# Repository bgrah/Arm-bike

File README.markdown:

Arm bike (ARM7 based system with GPS and graphical UI)
=============================================

Description
-----------

In this project is all about ARM, GPS, LCD, LED and bike. Throw all this together and make right connections and you have got a fine working and usable microcontroler system.
It's meant to be flexsible, modular, easy to use and of course open to all.

More about project description in Entry file below.

Documents
---------

+ [Entry file](https://github.com/blaaz15/Arm-bike/blob/master/project_description.markdown)

Current state:
--------------
+ 23. 4. 2012 -> First prototype PCB for MCU module (still waiting for parts from Farnell (13.5.))
+  1. 5. 2012 -> Started working on software.
+ 11. 5. 2012 -> Realized that the hardware part of project won't be finnished in time (still waiting for parts) :/
+ 13. 5. 2012 -> Software is comming nicely together. Still a lot of work, but its nice to see working things.

Author
------

Blaž Grah

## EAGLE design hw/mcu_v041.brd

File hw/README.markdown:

Arm-bike/hw
===========

TO-DO:
------
+ MCU PCB:
  - Put all pins on headers.
  - Improve design with separate analog and xtal ground.
  - Include mounting holes and round PCB edges.
  - Add schottky diodes on power input
  - Optimize header layout for multi-module layer use
+ SENSOR PCB:
  - Make place for GPS antenna
  - Leave free space for possible later additions (gyro,...)
+ TOUCHPAD PCB
  - Check MPR121 datasheet for touchpad dimensions/layout
  - Make space for LCD module
+ BIKE PCB
  - Design PWM enabled current supply for power LEDs
  - Battery powered with magnetic switch enable?
  - Voltage regulators from Vbat to 5V and 3.3V
+ LED holders
  - Sturdy, nice, water-resistant, easy to remove.
  - Good cooling

x_PCB
----------

### MCU PCB (`mcu_vxx.sch/.brd`)
##### Done: 50%

+ 23. 4. 2012  	`mcu_v052.brd` First prototype version. 
+ 23. 4. 2012   Waiting for parts to arrive

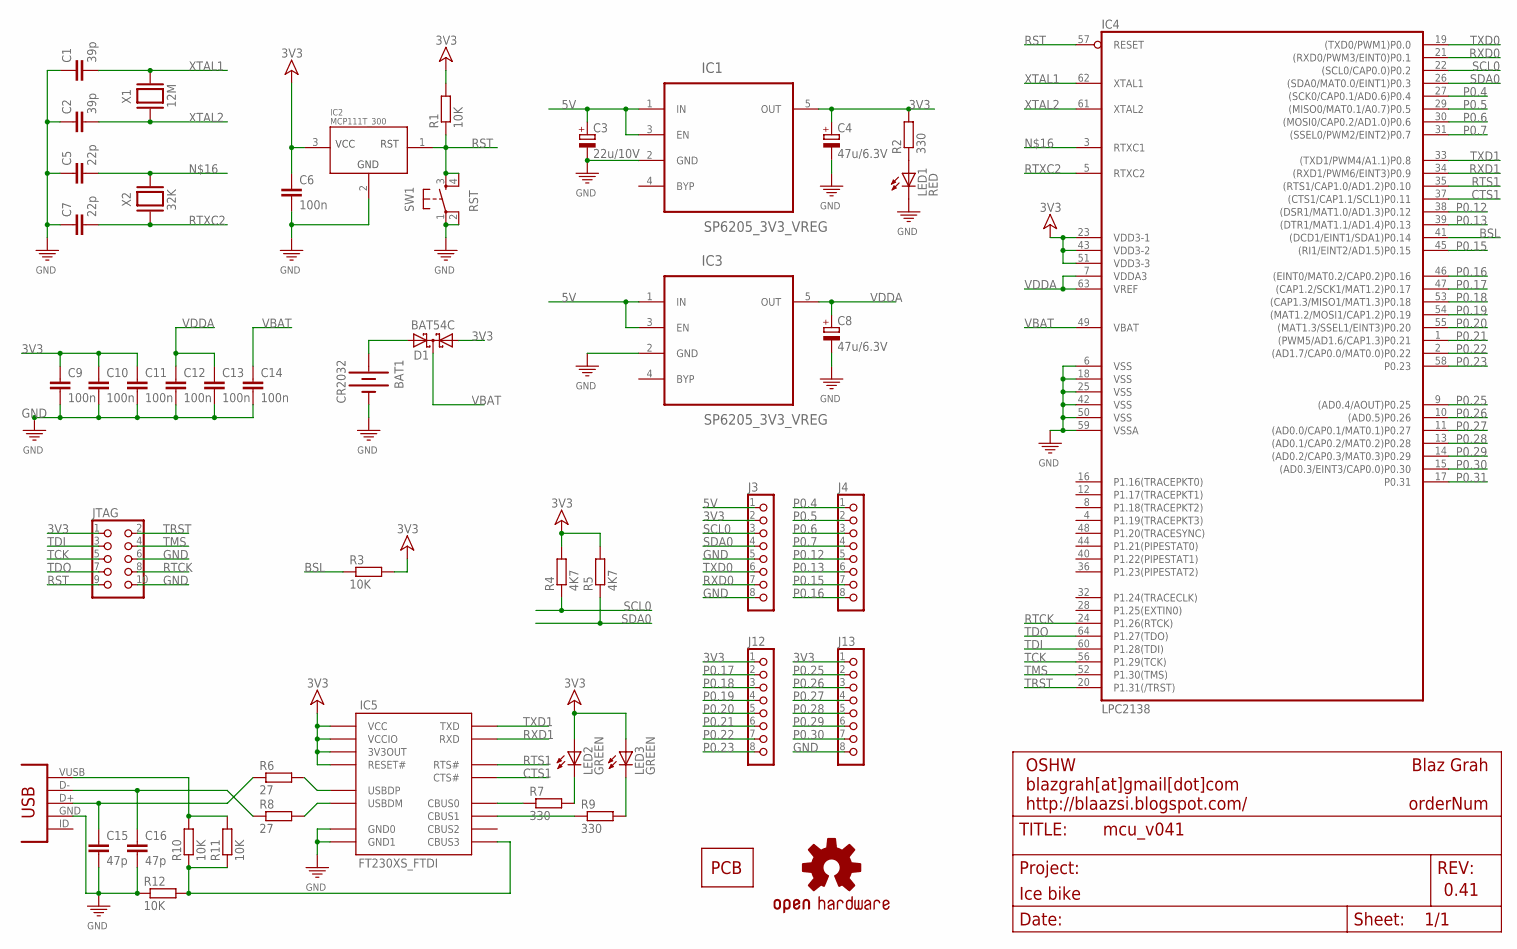
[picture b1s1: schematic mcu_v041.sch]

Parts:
BAT1: CR2032; BATTERY_20MM_SMD
C1, C2: 39p; C0603
C3: 22u/10V; SMC_B
C4, C8: 47u/6.3V; SMC_B
C5, C7: 22p; C0603
C6, C9, C10, C11, C12, C13, C14: 100n; C0603
C15, C16: 47p; C0603
D1: BAT54C; SOT23
DOC: FRAME_DINA4_L; DP_LOGO
IC1, IC3: SP6205_3V3_VREG; SOT23-5
IC2: MCP111T_300; SOT23
IC4: LPC2138; LQFP64
IC5: FT230XS_FTDI; SSOP16
J3, J4, J12, J13: CON_HEADER_1X08-PTH; M1X8
JTAG: CON_HEADER_2X05-PTH+SHROUDED_A; PINSHRD_PTH_2X05
LED1: RED; LED0805
LED2, LED3: GREEN; LED0805
LOGO1: OSHW-LOGOS; OSHW-LOGO-S
PCB1: PCB; PCB_50X50
R1, R3, R10, R11, R12: 10K; R0603
R2, R7, R9: 330; R0603
R4, R5: 4K7; R0603
R6, R8: 27; R0603
SW1: RST; BUTTON_SW_4P_SMD
USB1: CON-USB-F-MINI-B; CONN_USB_MINI-B
X1: 12M; CRYSTAL_12M_4.8X10.6MM
X2: 32K; CRYSTAL_32K_SMD

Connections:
3V3: C4.+, C6.1, C9.1, C10.1, C11.1, D1.1 (A1), IC1.5 (OUT), IC2.3 (VCC), IC4.23 (VDD3-1), IC4.43 (VDD3-2), IC4.51 (VDD3-3), IC5.P$3 (VCCIO), IC5.P$10 (3V3OUT), IC5.P$11 (RESET#), IC5.P$12 (VCC), J3.2, J12.1, J13.1, JTAG.1, LED2.A, LED3.A, R1.2, R2.2, R3.2, R4.2, R5.2
5V: C3.+, IC1.1 (IN), IC1.3 (EN), IC3.1 (IN), IC3.3 (EN), J3.1
BSL: IC4.41 ((DCD1/EINT1/SDA1)P0.14), R3.1
CTS1: IC4.37 ((CTS1/CAP1.1/SCL1)P0.11), IC5.P$6 (CTS#)
GND: BAT1.NEG, C1.1, C2.1, C3.-, C4.-, C5.1, C6.2, C7.1, C8.-, C9.2, C10.2, C11.2, C12.2, C13.2, C14.2, C15.2, C16.2, IC1.2 (GND), IC2.2 (GND), IC3.2 (GND), IC4.6 (VSS), IC4.18 (VSS), IC4.25 (VSS), IC4.42 (VSS), IC4.50 (VSS), IC4.59 (VSSA), IC5.P$5 (GND0), IC5.P$13 (GND1), J3.5, J3.8, J13.8, JTAG.6, JTAG.10, LED1.C, R12.1, SW1.1, SW1.2, USB1.GND
unnamed: LED1.A, R2.1
unnamed: BAT1.POS1 (POZ), BAT1.POS2 (POZ), D1.2 (A2)
unnamed: C16.1, R8.1, USB1.D-
unnamed: C15.1, R6.1, USB1.D+
unnamed: IC5.P$9 (USBDM), R8.2
unnamed: IC5.P$8 (USBDP), R6.2
unnamed: R10.2, R11.2, USB1.VUSB
unnamed: IC5.P$16 (CBUS3), R10.1, R11.1, R12.2
unnamed: IC5.P$14 (CBUS1), R9.1
unnamed: LED2.C, R7.2
unnamed: LED3.C, R9.2
unnamed: IC5.P$15 (CBUS0), R7.1
unnamed: C5.2, IC4.3 (RTXC1), X2.X2 (2)
P0.4: IC4.27 ((SCK0/CAP0.1/AD0.6)P0.4), J4.1
P0.5: IC4.29 ((MISO0/MAT0.1/A0.7)P0.5), J4.2
P0.6: IC4.30 ((MOSI0/CAP0.2/AD1.0)P0.6), J4.3
P0.7: IC4.31 ((SSEL0/PWM2/EINT2)P0.7), J4.4
P0.12: IC4.38 ((DSR1/MAT1.0/AD1.3)P0.12), J4.5
P0.13: IC4.39 ((DTR1/MAT1.1/AD1.4)P0.13), J4.6
P0.15: IC4.45 ((RI1/EINT2/AD1.5)P0.15), J4.7
P0.16: IC4.46 ((EINT0/MAT0.2/CAP0.2)P0.16), J4.8
P0.17: IC4.47 ((CAP1.2/SCK1/MAT1.2)P0.17), J12.2
P0.18: IC4.53 ((CAP1.3/MISO1/MAT1.3)P0.18), J12.3
P0.19: IC4.54 ((MAT1.2/MOSI1/CAP1.2)P0.19), J12.4
P0.20: IC4.55 ((MAT1.3/SSEL1/EINT3)P0.20), J12.5
P0.21: IC4.1 ((PWM5/AD1.6/CAP1.3)P0.21), J12.6
P0.22: IC4.2 ((AD1.7/CAP0.0/MAT0.0)P0.22), J12.7
P0.23: IC4.58 (P0.23), J12.8
P0.25: IC4.9 ((AD0.4/AOUT)P0.25), J13.2
P0.26: IC4.10 ((AD0.5)P0.26), J13.3
P0.27: IC4.11 ((AD0.0/CAP0.1/MAT0.1)P0.27), J13.4
P0.28: IC4.13 ((AD0.1/CAP0.2/MAT0.2)P0.28), J13.5
P0.29: IC4.14 ((AD0.2/CAP0.3/MAT0.3)P0.29), J13.6
P0.30: IC4.15 ((AD0.3/EINT3/CAP0.0)P0.30), J13.7
P0.31: IC4.17 (P0.31)
RST: IC2.1 (RST), IC4.57 (RESET), JTAG.9, R1.1, SW1.3, SW1.4
RTCK: IC4.24 (P1.26(RTCK)), JTAG.8
RTS1: IC4.35 ((RTS1/CAP1.0/AD1.2)P0.10), IC5.P$2 (RTS#)
RTXC2: C7.2, IC4.5 (RTXC2), X2.X1 (1)
RXD0: IC4.21 ((RXD0/PWM3/EINT0)P0.1), J3.7
RXD1: IC4.34 ((RXD1/PWM6/EINT3)P0.9), IC5.P$4 (RXD)
SCL0: IC4.22 ((SCL0/CAP0.0)P0.2), J3.3, R4.1
SDA0: IC4.26 ((SDA0/MAT0.0/EINT1)P0.3), J3.4, R5.1
TCK: IC4.56 (P1.29(TCK)), JTAG.5
TDI: IC4.60 (P1.28(TDI)), JTAG.3
TDO: IC4.64 (P1.27(TDO)), JTAG.7
TMS: IC4.52 (P1.30(TMS)), JTAG.4
TRST: IC4.20 (P1.31(/TRST)), JTAG.2
TXD0: IC4.19 ((TXD0/PWM1)P0.0), J3.6
TXD1: IC4.33 ((TXD1/PWM4/A1.1)P0.8), IC5.P$1 (TXD)
VBAT: C14.1, D1.3 (CC), IC4.49 (VBAT)
VDDA: C8.+, C12.1, C13.1, IC3.5 (OUT), IC4.7 (VDDA3), IC4.63 (VREF)
XTAL1: C1.2, IC4.62 (XTAL1), X1.P$2 (2)
XTAL2: C2.2, IC4.61 (XTAL2), X1.P$1 (1)

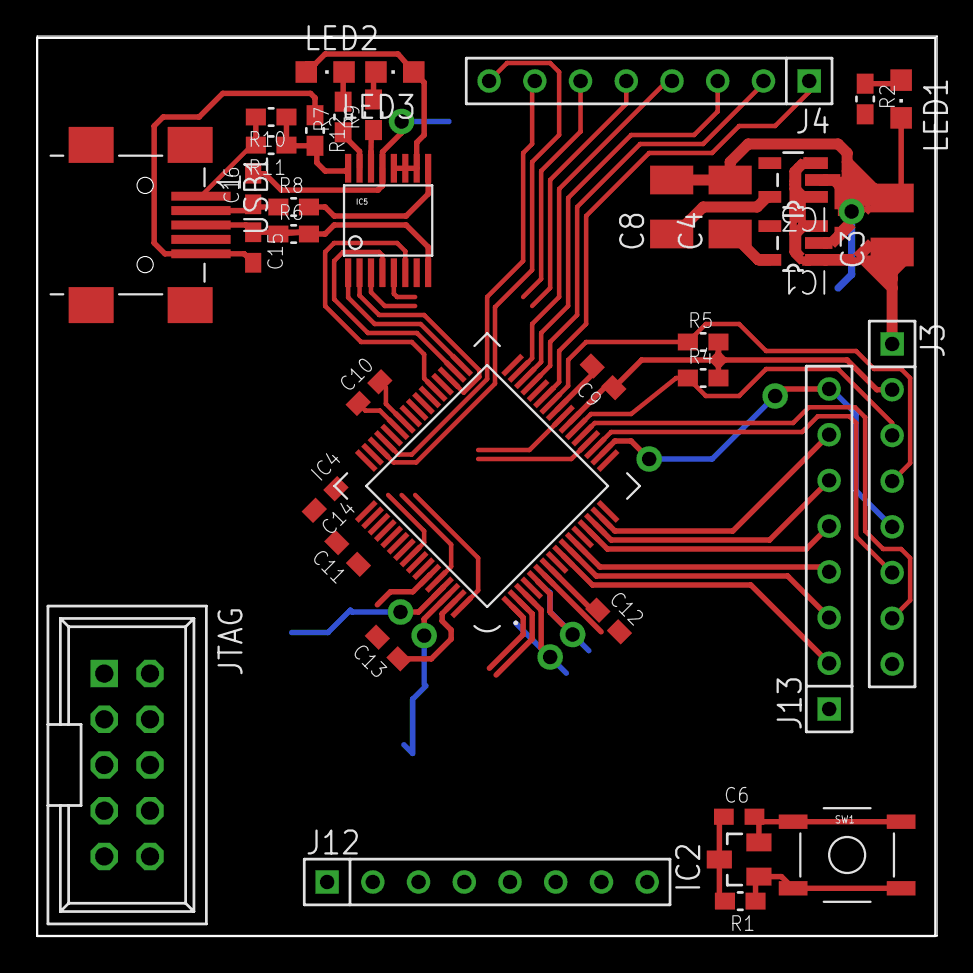
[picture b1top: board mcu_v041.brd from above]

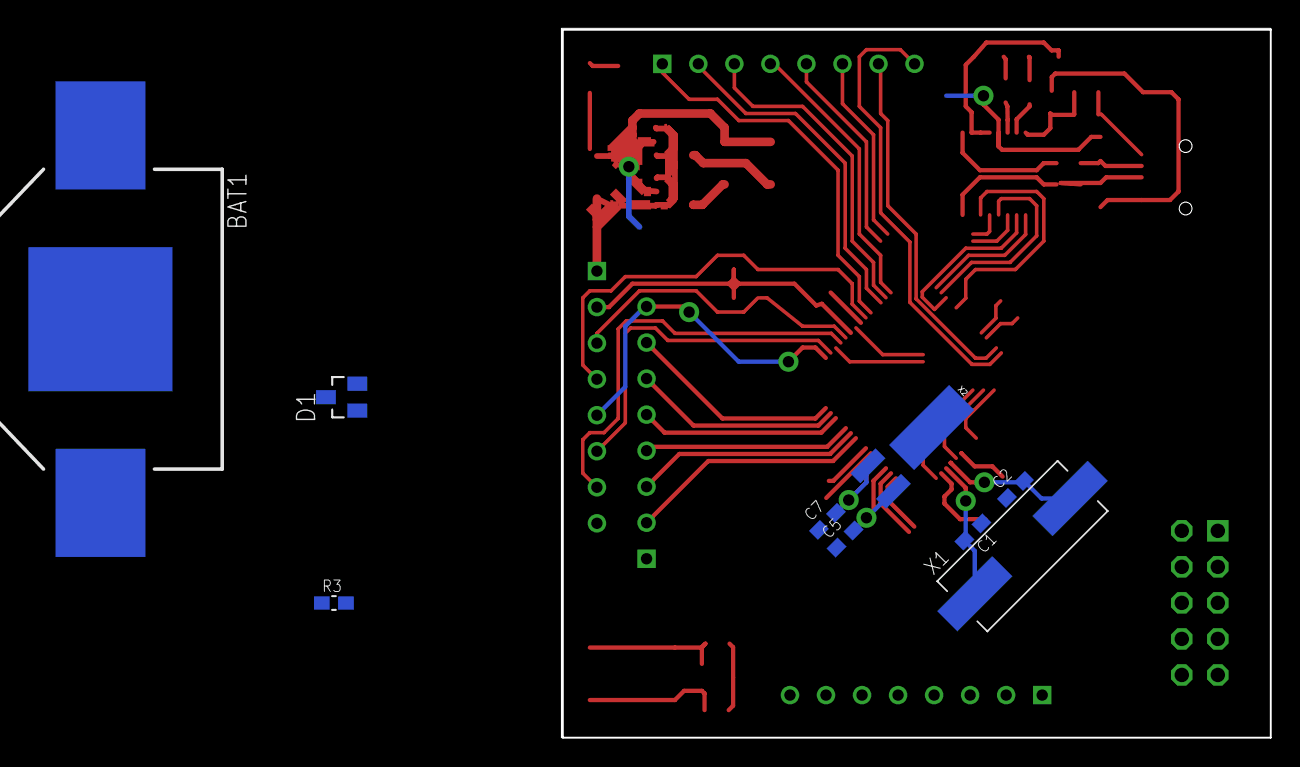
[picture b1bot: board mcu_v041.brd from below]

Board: 2 copper layers, 50.0 x 50.0 mm, 50 parts (9 on the bottom side), 58 nets.

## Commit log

2012-05-07 Added README.markdown
2012-05-07 Started new repo.
2012-05-09 Comenting GLCD_driver code.
2012-05-09 Fully commented GLCD_driver.c/.h.
2012-05-12 Added I2C lib. Started on writing code for Touch pads.
2012-05-13 Started interfacing MPR121 with i2c.
2012-05-13 More work on MPR121 lib. Sleep time.
2012-05-13 More work on MPR121... still not working.
2012-05-14 More work on I2C. Started GPS uart.
2012-05-15 Working i2c!! ;)
2012-05-15 Modify README.markdown
2012-05-16 Working i2c touch, UART GPS and PWM LED. :)
2012-09-14 Working GPS uart, GLCD, GPC i2c. New branch, to complete the GIU and add OS.
2012-09-14 Sorting GPS sentences to different strings. Done.
2012-09-15 Added data separation from gps sentences. Speed, coordintates, time, satelites, fix status.
2012-09-16 Added few status icons (signal strength, battery), printout for gps height.
2012-09-16 Last working version before RTOS2.
2012-09-19 Added different screens, moving with buttons.
2012-09-19 Height and speed graphs are working. 1min scale. Added reset button for graphs and statistic.
2012-10-16 New code.

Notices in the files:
hw/mcu_v041.brd:
LICENSE: OSHW
parts and their libraries:
11_SparkFun: Licensing: CC v3.0 Share-Alike You are welcome to use this library for commercial purposes.
